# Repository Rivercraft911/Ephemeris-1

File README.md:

# Ephemeris 1

Tired of $10,000 spacecraft GNSS quotes? About $33 in parts buys the front end of our own GPS L1 receiver.

The MAX2769B takes GPS L1 in through the SMA and sends raw I/Q samples to the host header. Receiver firmware targets an RP2350B. The first boards are here for assembly and Safran simulator testing follows bring-up.

[Interactive assembly BOM](https://rivercraft911.github.io/Ephemeris-1/assembly/ibom.html) · [Parts and cost](docs/ordering-bom.md) · [KiCad](hardware/GNSS-IQ-Breakout.kicad_pro) · [Bring-up](docs/design.md#first-capture) · [Receiver](docs/software/receiver.md) · [Ground fix](docs/software/ground.md) · [Orbital fix timing](docs/software/orbit-fix.md) · [Test plots](docs/software/results.md)

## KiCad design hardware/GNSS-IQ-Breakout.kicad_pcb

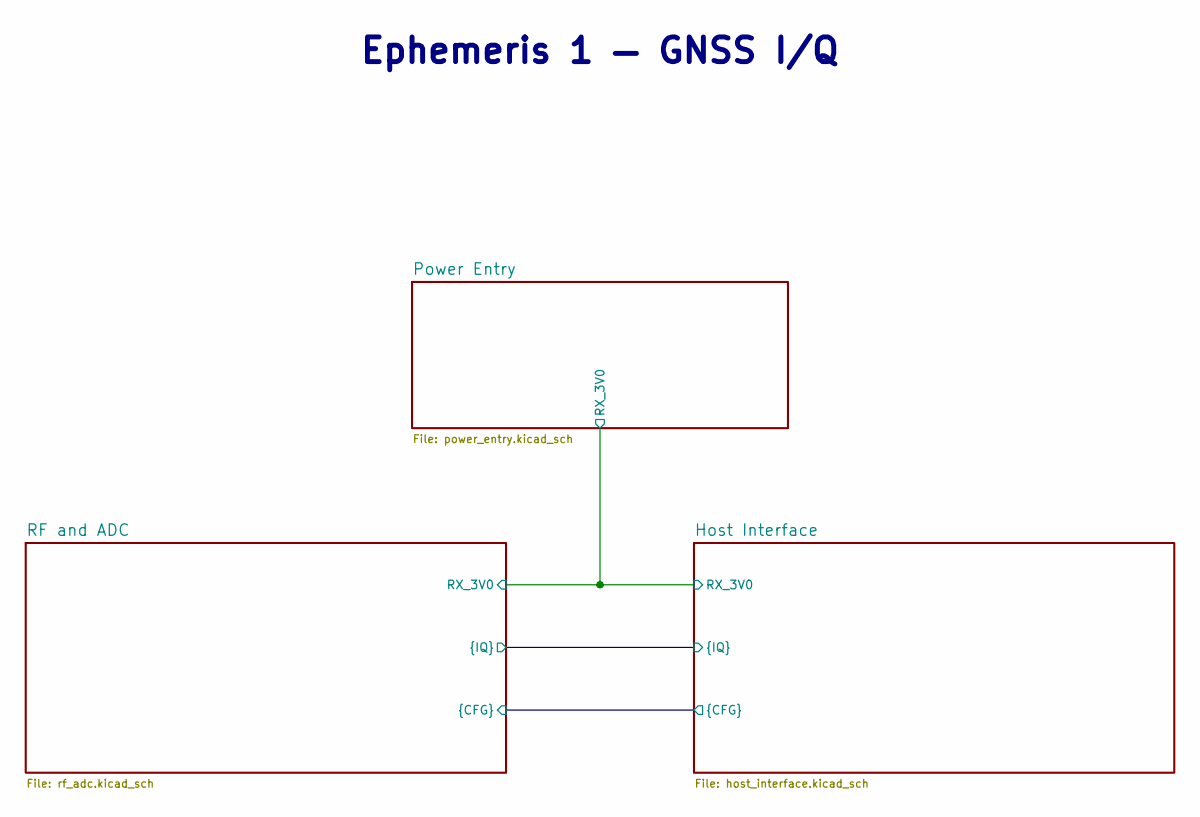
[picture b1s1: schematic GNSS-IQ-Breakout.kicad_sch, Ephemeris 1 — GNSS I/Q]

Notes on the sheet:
Ephemeris 1 — GNSS I/Q

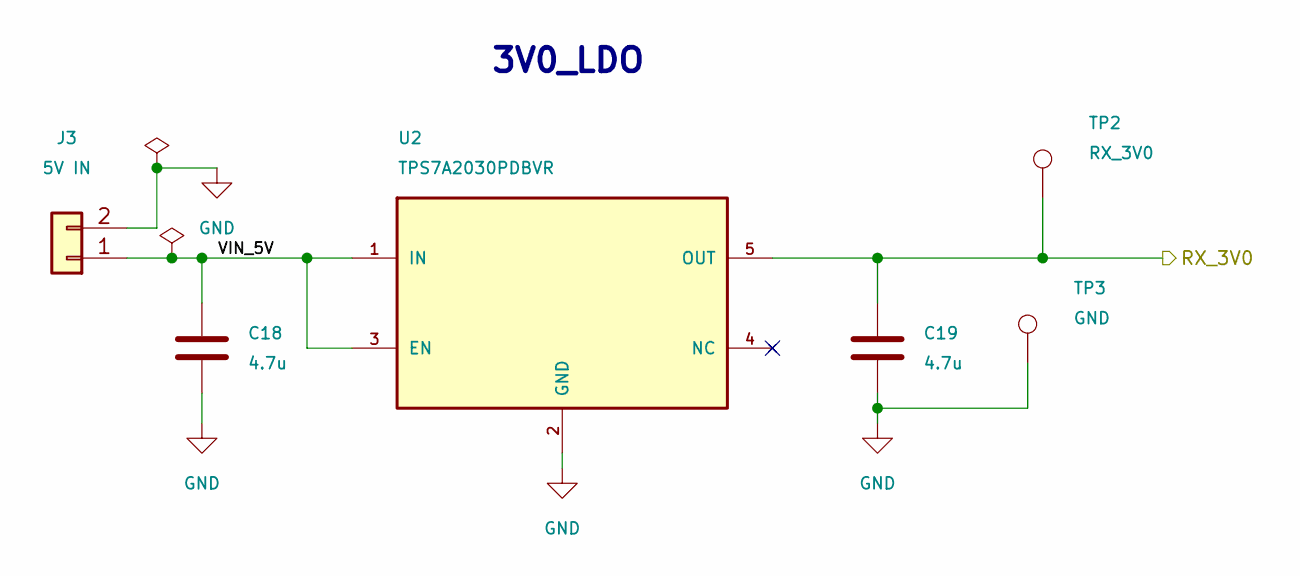
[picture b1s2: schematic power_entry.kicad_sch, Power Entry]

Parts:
C18, C19: 4.7u; C_0805_2012Metric; MPN C2012X7R1E475K125AB
J3: 5V IN; Wuerth_61300211121_1x02; MPN 61300211121
TP2: RX_3V0; TestPoint_Pad_D1.5mm
TP3: GND; TestPoint_Pad_D1.5mm
U2: TPS7A2030PDBVR; SOT-23-5; MPN TPS7A2030PDBVR

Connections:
/Host Interface/RX_3V0: C19.1, TP2.1 (1_1), U2.5 (OUT); also elsewhere on the board
/Power Entry/VIN_5V: C18.1, J3.1, U2.1 (IN), U2.3 (EN)
GND: C18.2, C19.2, J3.2, TP3.1 (1_1), U2.2 (GND); also elsewhere on the board

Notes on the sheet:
3V0_LDO

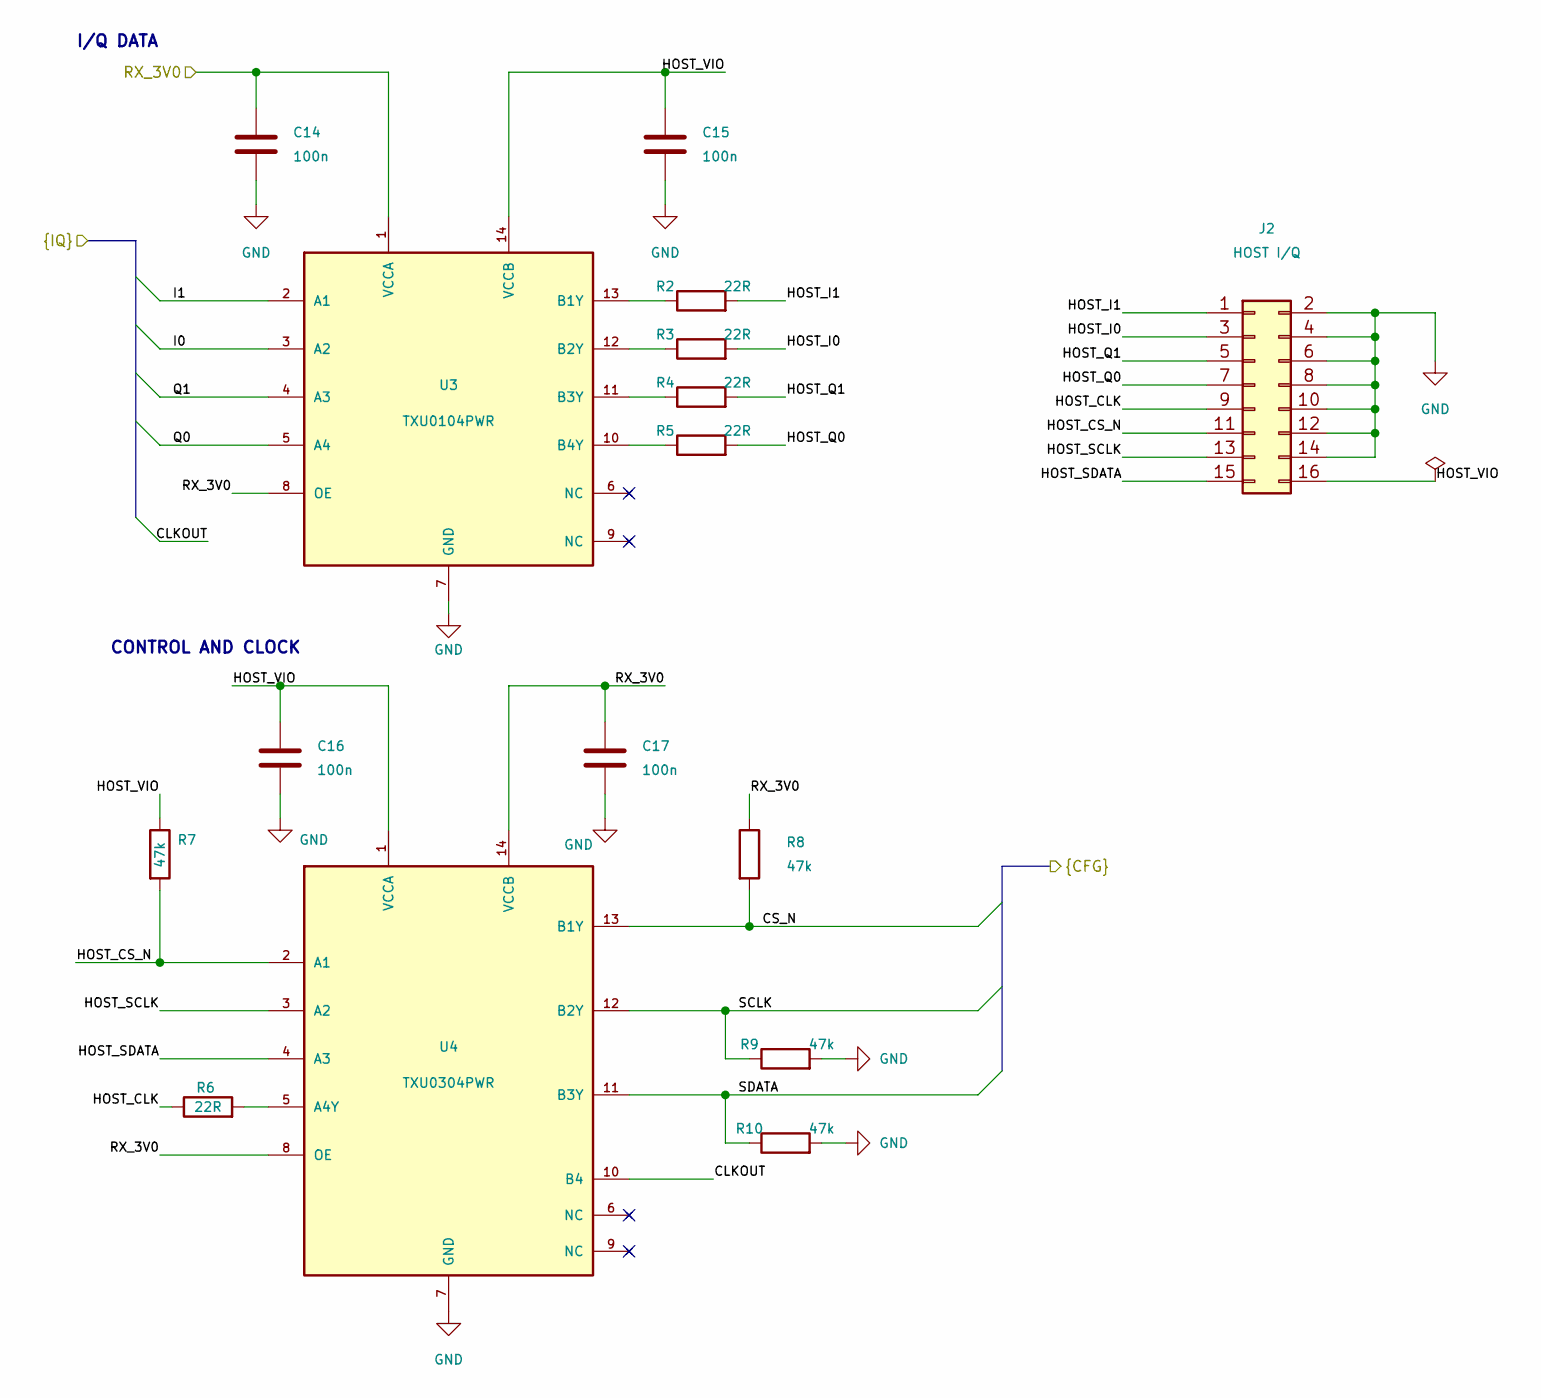
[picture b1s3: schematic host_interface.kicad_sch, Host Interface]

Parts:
C14, C15, C16, C17: 100n; C_0603_1608Metric; MPN GRM188R71C104KA01D
J2: HOST I/Q; Wuerth_61301621121_2x08; MPN 61301621121
R2, R3, R4, R5, R6: 22R; R_0603_1608Metric; MPN RC0603FR-0722RL
R7, R8, R9, R10: 47k; R_0603_1608Metric; MPN RC0603FR-0747KL
U3: TXU0104PWR; TSSOP-14_4.4x5mm_P0.65mm; MPN TXU0104PWR
U4: TXU0304PWR; TSSOP-14_4.4x5mm_P0.65mm; MPN TXU0304PWR

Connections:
/Host Interface/CLKOUT: U4.10 (B4); also elsewhere on the board
/Host Interface/CS_N: R8.2, U4.13 (B1Y); also elsewhere on the board
/Host Interface/HOST_CLK: J2.9, R6.1
/Host Interface/HOST_CS_N: J2.11, R7.2, U4.2 (A1)
/Host Interface/HOST_I0: J2.3, R3.2
/Host Interface/HOST_I1: J2.1, R2.2
/Host Interface/HOST_Q0: J2.7, R5.2
/Host Interface/HOST_Q1: J2.5, R4.2
/Host Interface/HOST_SCLK: J2.13, U4.3 (A2)
/Host Interface/HOST_SDATA: J2.15, U4.4 (A3)
/Host Interface/HOST_VIO: C15.1, C16.1, J2.16, R7.1, U3.14 (VCCB), U4.1 (VCCA)
/Host Interface/I0: U3.3 (A2); also elsewhere on the board
/Host Interface/I1: U3.2 (A1); also elsewhere on the board
/Host Interface/Q0: U3.5 (A4); also elsewhere on the board
/Host Interface/Q1: U3.4 (A3); also elsewhere on the board
/Host Interface/RX_3V0: C14.1, C17.1, R8.1, U3.1 (VCCA), U3.8 (OE), U4.8 (OE), U4.14 (VCCB); also elsewhere on the board
/Host Interface/SCLK: R9.1, U4.12 (B2Y); also elsewhere on the board
/Host Interface/SDATA: R10.1, U4.11 (B3Y); also elsewhere on the board
GND: C14.2, C15.2, C16.2, C17.2, J2.2, J2.4, J2.6, J2.8, J2.10, J2.12, J2.14, R9.2, R10.2, U3.7 (GND), U4.7 (GND); also elsewhere on the board
unnamed: R2.1, U3.13 (B1Y)
unnamed: R3.1, U3.12 (B2Y)
unnamed: R4.1, U3.11 (B3Y)
unnamed: R5.1, U3.10 (B4Y)
unnamed: R6.2, U4.5 (A4Y)

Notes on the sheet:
I/Q DATA
CONTROL AND CLOCK

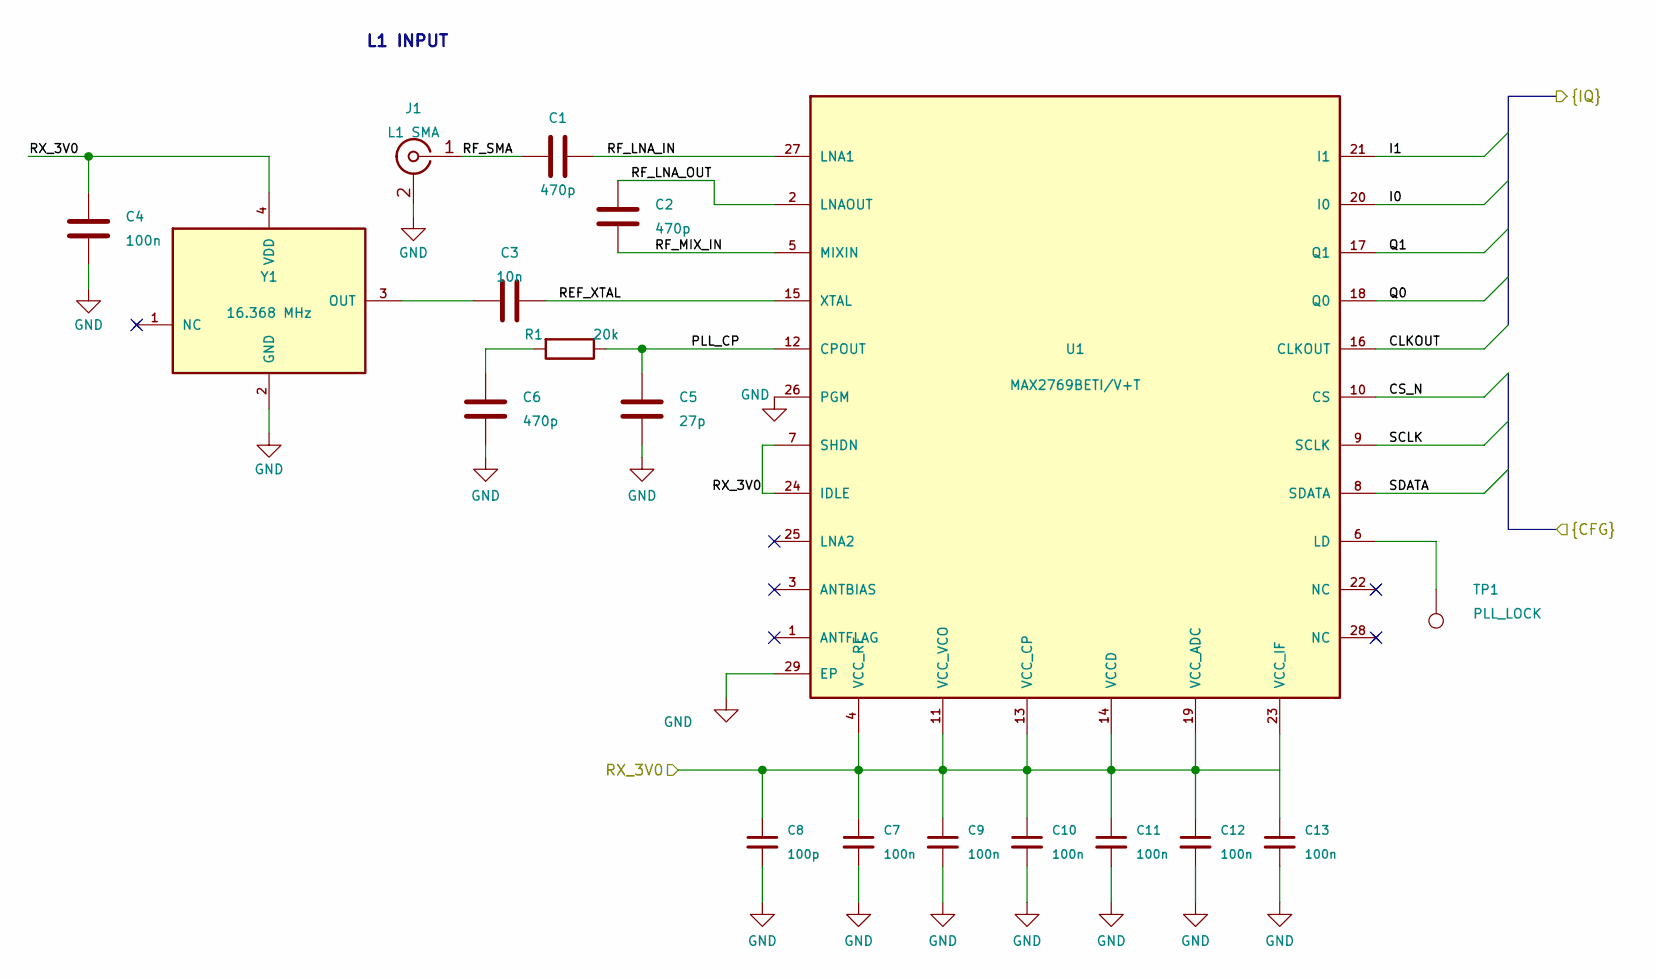
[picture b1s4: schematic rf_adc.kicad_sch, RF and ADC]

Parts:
C1, C2, C6: 470p; C_0402_1005Metric; MPN GRM1555C1H471JA01D
C3: 10n; C_0402_1005Metric; MPN GRM155R71H103KA88D
C4: 100n; C_0603_1608Metric; MPN GRM188R71C104KA01D
C5: 27p; C_0402_1005Metric; MPN GRM1555C1H270JA01D
C7, C9, C10, C11, C12, C13: 100n; C_0402_1005Metric; MPN GRM155R71C104KA88D
C8: 100p; C_0402_1005Metric; MPN GRM1555C1H101JA01D
J1: L1 SMA; Samtec_SMA_J_P_H_ST_EM3_DropInEdge; MPN SMA-J-P-H-ST-EM3
R1: 20k; R_0603_1608Metric; MPN RC0603FR-0720KL
TP1: PLL_LOCK; TestPoint_Pad_D1.5mm
U1: MAX2769BETI/V+T; TQFN-28-1EP_ADI_90-0023; MPN MAX2769BETI/V+T
Y1: 16.368 MHz; Taitien_TX_3.2x2.5mm; MPN TXETCDSANF-16.368000

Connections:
/Host Interface/CLKOUT: U1.16 (CLKOUT); also elsewhere on the board
/Host Interface/CS_N: U1.10 (CS); also elsewhere on the board
/Host Interface/I0: U1.20 (I0); also elsewhere on the board
/Host Interface/I1: U1.21 (I1); also elsewhere on the board
/Host Interface/Q0: U1.18 (Q0); also elsewhere on the board
/Host Interface/Q1: U1.17 (Q1); also elsewhere on the board
/Host Interface/RX_3V0: C4.1, C7.1, C8.1, C9.1, C10.1, C11.1, C12.1, C13.1, U1.4 (VCC_RF), U1.7 (SHDN), U1.11 (VCC_VCO), U1.13 (VCC_CP), U1.14 (VCCD), U1.19 (VCC_ADC), U1.23 (VCC_IF), U1.24 (IDLE), Y1.4 (VDD); also elsewhere on the board
/Host Interface/SCLK: U1.9 (SCLK); also elsewhere on the board
/Host Interface/SDATA: U1.8 (SDATA); also elsewhere on the board
/RF and ADC/PLL_CP: C5.1, R1.1, U1.12 (CPOUT)
/RF and ADC/REF_XTAL: C3.2, U1.15 (XTAL)
/RF and ADC/RF_LNA_IN: C1.2, U1.27 (LNA1)
/RF and ADC/RF_LNA_OUT: C2.1, U1.2 (LNAOUT)
/RF and ADC/RF_MIX_IN: C2.2, U1.5 (MIXIN)
/RF and ADC/RF_SMA: C1.1, J1.1 (In)
GND: C4.2, C5.2, C6.2, C7.2, C8.2, C9.2, C10.2, C11.2, C12.2, C13.2, J1.2 (Ext), U1.26 (PGM), U1.29 (EP), Y1.2 (GND); also elsewhere on the board
unnamed: C6.1, R1.2
unnamed: TP1.1 (1_1), U1.6 (LD)
unnamed: C3.1, Y1.3 (OUT)

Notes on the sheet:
L1 INPUT

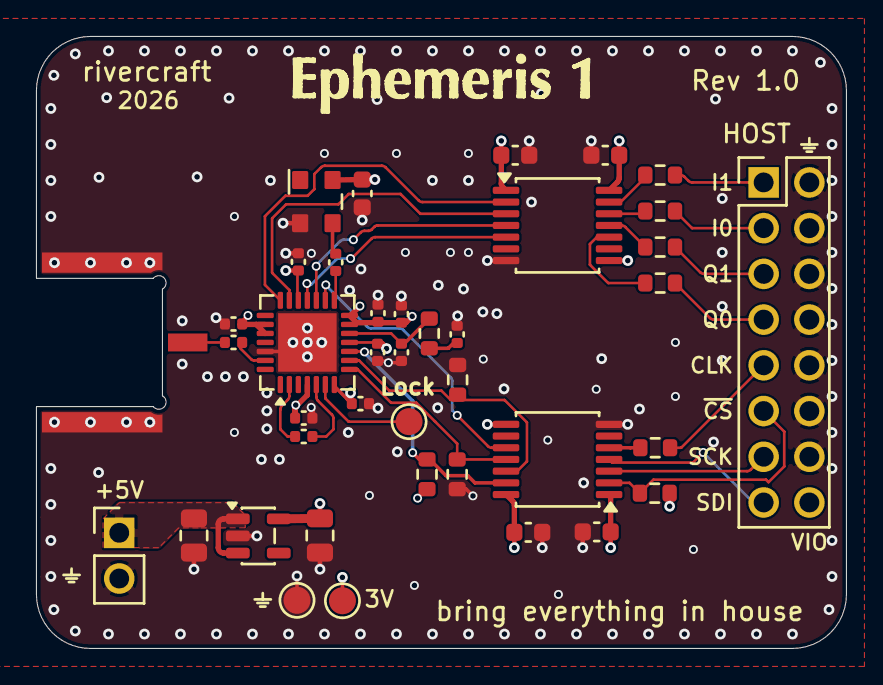
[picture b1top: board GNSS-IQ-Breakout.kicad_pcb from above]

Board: 4 copper layers, 45.0 x 34.0 mm, 40 parts (0 on the bottom side), 34 nets.

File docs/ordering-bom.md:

# Ephemeris 1 parts and assembly

One board takes **37 parts across 18 order lines**, all placed on the front. TP1–TP3 are bare copper. Use the interactive BOM to find pin 1, highlight pads and check off placements. It shows schematic MPNs. The table below includes the purchasing substitutions marked †. [Interactive assembly BOM](assembly/ibom.html) · [Reflow and connector assembly](design.md#footprints-and-hot-plate-assembly)

## Cost per board

The listed parts total **$32.96 per board** using the installed quantities and DigiKey US quantity-one prices checked November 18, 2026. The ICs and oscillator account for $19.63, the connectors $9.25, the capacitors $3.08 and the resistors $1.00. This estimate excludes the bare PCB, stencil, spares, tax, shipping, labor, antenna and capture host.

For context, Pumpkin lists its flight-qualified GPSRM 1 receiver kit from $11,485. That kit computes position, velocity and time. Ephemeris 1 is at the raw-sample stage of an in-house receiver. [Pumpkin GPSRM 1](https://www.pumpkinspace.com/store/p58/GNSS_Receiver_Module_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

## Order lines

Prices are USD per part. The two-board buy quantities allow for hand-assembly spares. Use cut tape for SMT parts and single pieces for connectors.

| References | Part | Purchase MPN · DigiKey | DigiKey SKU | Qty / board | Buy for 2 with spares | Unit price |
| --- | --- | --- | --- | ---: | ---: | ---: |
| U1 | GNSS RF receiver, TQFN-28 | [MAX2769BETI/V+T](https://www.digikey.com/en/products/detail/analog-devices-in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 | 175-MAX2769BETI/V+TCT-ND | 1 | 2 | $14.28 |
| U2 | 3.0 V LDO, SOT-23-5 | [TPS7A2030PDBVR](https://www.digikey.com/en/products/detail/texas-instruments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 | 296-TPS7A2030PDBVRCT-ND | 1 | 2 | $0.35 |
| U3 | 4-channel I/Q translator, TSSOP-14 | [TXU0104QPWRQ1](https://www.digikey.com/en/products/detail/texas-instruments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 † | 296-TXU0104QPWRQ1CT-ND | 1 | 2 | $1.30 |
| U4 | Control/clock translator, TSSOP-14 | [TXU0304PWR](https://www.digikey.com/en/products/detail/texas-instruments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 | 296-TXU0304PWRCT-ND | 1 | 2 | $1.05 |
| Y1 | 16.368 MHz TCXO, 3.2 × 2.5 mm | [TXETCDSANF-16.368000](https://www.digikey.com/en/products/detail/taitien/TXETCDSAN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 | 1664-TXETCDSANF-16.368000CT-ND | 1 | 2 | $2.65 |
| J1 | Samtec SMA jack, EM3 notch mount | [SMA-J-P-H-ST-EM3](https://www.digikey.com/en/products/detail/samtec-inc/SMA-J-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 | SAM9950-ND | 1 | 2 | $8.12 |
| J2 | 2×8 male header, 2.54 mm | [61301621121](https://www.digikey.com/en/products/detail/w%C3%BCrth-elektr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 | 732-5299-ND | 1 | 2 | $1.00 |
| J3 | 1×2 male header, 2.54 mm | [61300211121](https://www.digikey.com/en/products/detail/w%C3%BCrth-elektr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 | 732-5315-ND | 1 | 2 | $0.13 |
| C1, C2, C6 | 470 pF, C0G, 50 V, 5%, 0402 | [GRM1555C1H471JA01D](https://www.digikey.com/en/products/detail/murata-electronic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 | 490-1297-1-ND | 3 | 10 | $0.10 |
| C3 | 10 nF, X7R, 50 V, 10%, 0402 | [GRM155R71H103KA88D](https://www.digikey.com/en/products/detail/murata-electronic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 | 490-4516-1-ND | 1 | 10 | $0.10 |
| C5 | 27 pF, C0G, 50 V, 5%, 0402 | [GRM1555C1H270JA01D](https://www.digikey.com/en/products/detail/murata-electronic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 | 490-5869-1-ND | 1 | 10 | $0.10 |
| C8 | 100 pF, C0G, 50 V, 5%, 0402 | [GRM1555C1H101JA01J](https://www.digikey.com/en/products/detail/murata-electronic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 † | 490-7754-1-ND | 1 | 10 | $0.10 |
| C7, C9, C10, C11, C12, C13 | 100 nF, X7R, 16 V, 10%, 0402 | [GRM155R71C104KA88J](https://www.digikey.com/en/products/detail/murata-electronic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 † | 490-6328-1-ND | 6 | 20 | $0.10 |
| C4, C14, C15, C16, C17 | 100 nF, X7R, 16 V, 10%, 0603 | [CC0603KRX7R7BB104](https://www.digikey.com/en/products/detail/yageo/CC0603KRX7R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 † | 311-1088-1-ND | 5 | 20 | $0.14 |
| C18, C19 | 4.7 µF, X7R, 35 V, 10%, 0805 | [C2012X7R1V475K125AC](https://www.digikey.com/en/products/detail/tdk-corporation/C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 † | 445-7555-1-ND | 2 | 10 | $0.59 |
| R1 | 20 kΩ, 1%, 0.1 W, 0603 | [RC0603FR-0720KL](https://www.digikey.com/en/products/detail/yageo/RC0603FR-07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 | 311-20.0KHRCT-ND | 1 | 10 | $0.10 |
| R2, R3, R4, R5, R6 | 22 Ω, 1%, 0.1 W, 0603 | [AC0603FR-0722RL](https://www.digikey.com/en/products/detail/yageo/AC0603FR-07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 † | YAG3581CT-ND | 5 | 20 | $0.10 |
| R7, R8, R9, R10 | 47 kΩ, 1%, 0.1 W, 0603 | [RC0603FR-0747KL](https://www.digikey.com/en/products/detail/yageo/RC0603FR-07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 | 311-47.0KHRCT-ND | 4 | 10 | $0.10 |

## Purchasing substitutions

The original ordering review on November 6, 2026 recorded the following substitutions. See the linked listings for current availability.

- U3: TXU0104PWR was backordered at review; TXU0104QPWRQ1 uses the same PW TSSOP-14 footprint/pin map, four A→B channels, active-high OE and suitable rail range. Automotive qualification is added. [Original TI datasheet](https://www.ti.com/lit/ds/symlink/txu0104.pdf) · [Q1 datasheet](https://www.ti.com/lit/ds/symlink/txu0104-q1.pdf)
- C8 and C7/C9–C13: the Murata D→J suffix changes the reel packaging; electrical values and bodies are unchanged. The listed DigiKey cut-tape SKUs avoid buying reels.
- C4/C14–C17: obsolete Murata GRM188R71C104KA01D is replaced by Yageo CC0603KRX7R7BB104, matching 100 nF, ±10%, X7R, 16 V and 0603 body.
- R2–R6: backordered RC0603FR-0722RL is replaced by automotive AC0603FR-0722RL, matching 22 Ω, ±1%, 0.1 W, 0603 and ±100 ppm/°C.
- C18/C19: backordered TDK C2012X7R1E475K125AB is replaced by C2012X7R1V475K125AC, 4.7 µF ±10%, X7R, **35 V** rather than 25 V, with the same nominal 2.0 × 1.25 × 1.25 mm body. Reading the exact TDK characterization curve supports conservative 20% loss at 5.25 V and 10% at 3.045 V; after −10% tolerance and −15% temperature, estimates are **2.88 µF input / 3.24 µF output before aging**. These typical-curve estimates preserve the previous capacitor margin, not a guaranteed worst-case capacitance. [TDK characterization](https://docs.rs-online.com/1d3c/A700000006893460.pdf)
